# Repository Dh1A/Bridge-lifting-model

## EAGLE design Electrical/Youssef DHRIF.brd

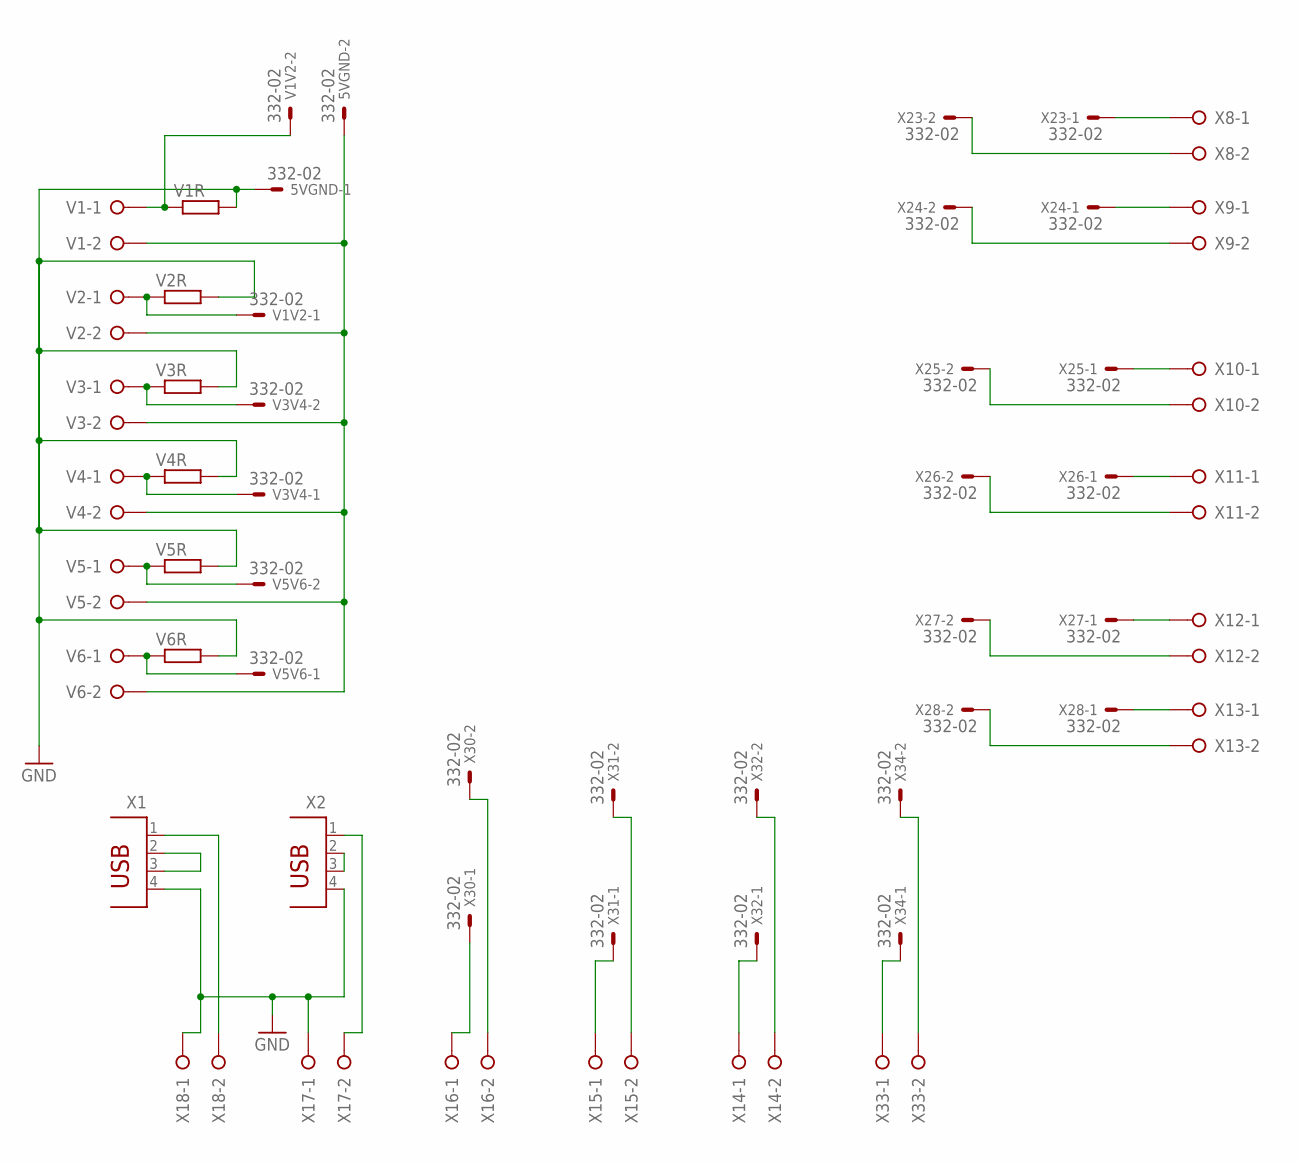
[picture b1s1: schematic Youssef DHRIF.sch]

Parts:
5VGND: 332-02
V1, V2, V3, V4, V5, V6: W237-02P; W237-132
V1R, V2R, V3R, V4R, V5R, V6R: R0207/10; 0207/10
V1V2, V3V4, V5V6: 332-02
X1, X2: PN87520
X8, X9, X10, X11, X12, X13, X14, X15, X16, X17, X18, X33: W237-02P; W237-132
X23, X24, X25, X26, X27, X28, X30, X31, X32, X34: 332-02

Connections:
GND: 5VGND.1, V1R.2, V2R.2, V3R.2, V4R.2, V5R.2, V6R.2, X1.4, X2.4, X17.1, X18.1
unnamed: 5VGND.2, V1.2, V2.2, V3.2, V4.2, V5.2, V6.2
unnamed: V5V6.1, V6.1, V6R.1
unnamed: V5.1, V5R.1, V5V6.2
unnamed: V3V4.1, V4.1, V4R.1
unnamed: V3.1, V3R.1, V3V4.2
unnamed: V1V2.1, V2.1, V2R.1
unnamed: V1.1, V1R.1, V1V2.2
unnamed: X8.1, X23.1
unnamed: X8.2, X23.2
unnamed: X9.1, X24.1
unnamed: X9.2, X24.2
unnamed: X10.1, X25.1
unnamed: X10.2, X25.2
unnamed: X11.1, X26.1
unnamed: X11.2, X26.2
unnamed: X12.1, X27.1
unnamed: X12.2, X27.2
unnamed: X13.1, X28.1
unnamed: X13.2, X28.2
unnamed: X1.1, X18.2
unnamed: X1.2, X1.3
unnamed: X2.1, X17.2
unnamed: X2.2, X2.3
unnamed: X16.1, X30.1
unnamed: X16.2, X30.2
unnamed: X15.1, X31.1
unnamed: X15.2, X31.2
unnamed: X14.1, X32.1
unnamed: X14.2, X32.2
unnamed: X33.1, X34.1
unnamed: X33.2, X34.2

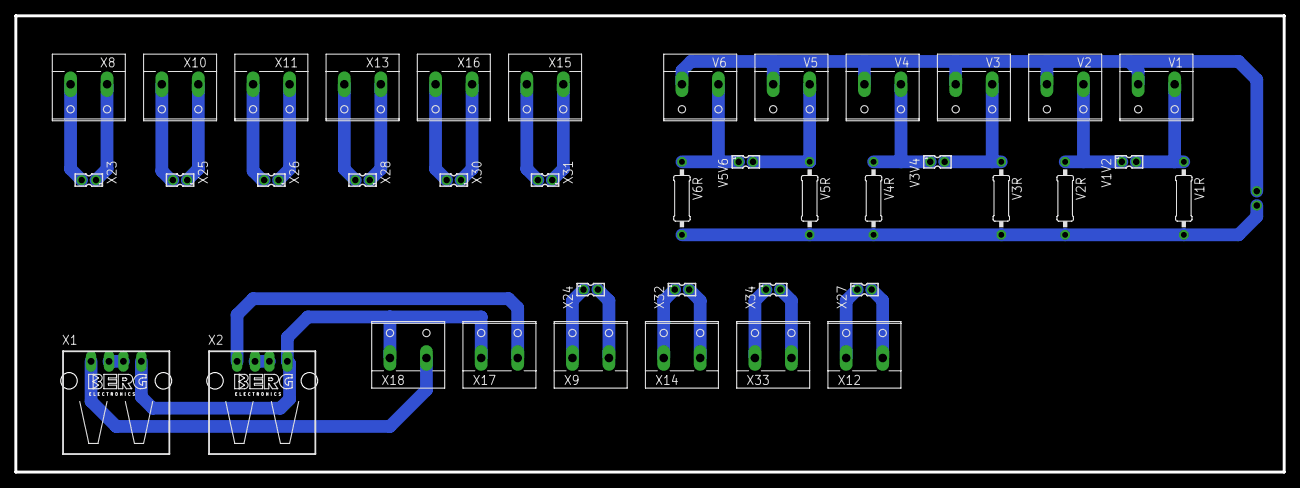
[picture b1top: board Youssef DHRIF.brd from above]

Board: 2 copper layers, 176.5 x 63.5 mm, 40 parts (1 on the bottom side), 32 nets.

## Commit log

2017-11-13 :octocat: Added .gitattributes & .gitignore files
2017-11-13 Brigde Lifting Model
    Brigde Lifting Model
